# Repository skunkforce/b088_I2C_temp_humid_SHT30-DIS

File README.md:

# edgy_board number b088
This design is part of the [edgy board project](https://github.com/skunkforce/edgy_boards).

# getting started
This repository uses submodules. After cloning use the command 

```$ git submodule update --init --recursive```

to pull the submodules before opening the project with kicad. 

# Tests
Tests can be found in [TESTS.md](TESTS.md)

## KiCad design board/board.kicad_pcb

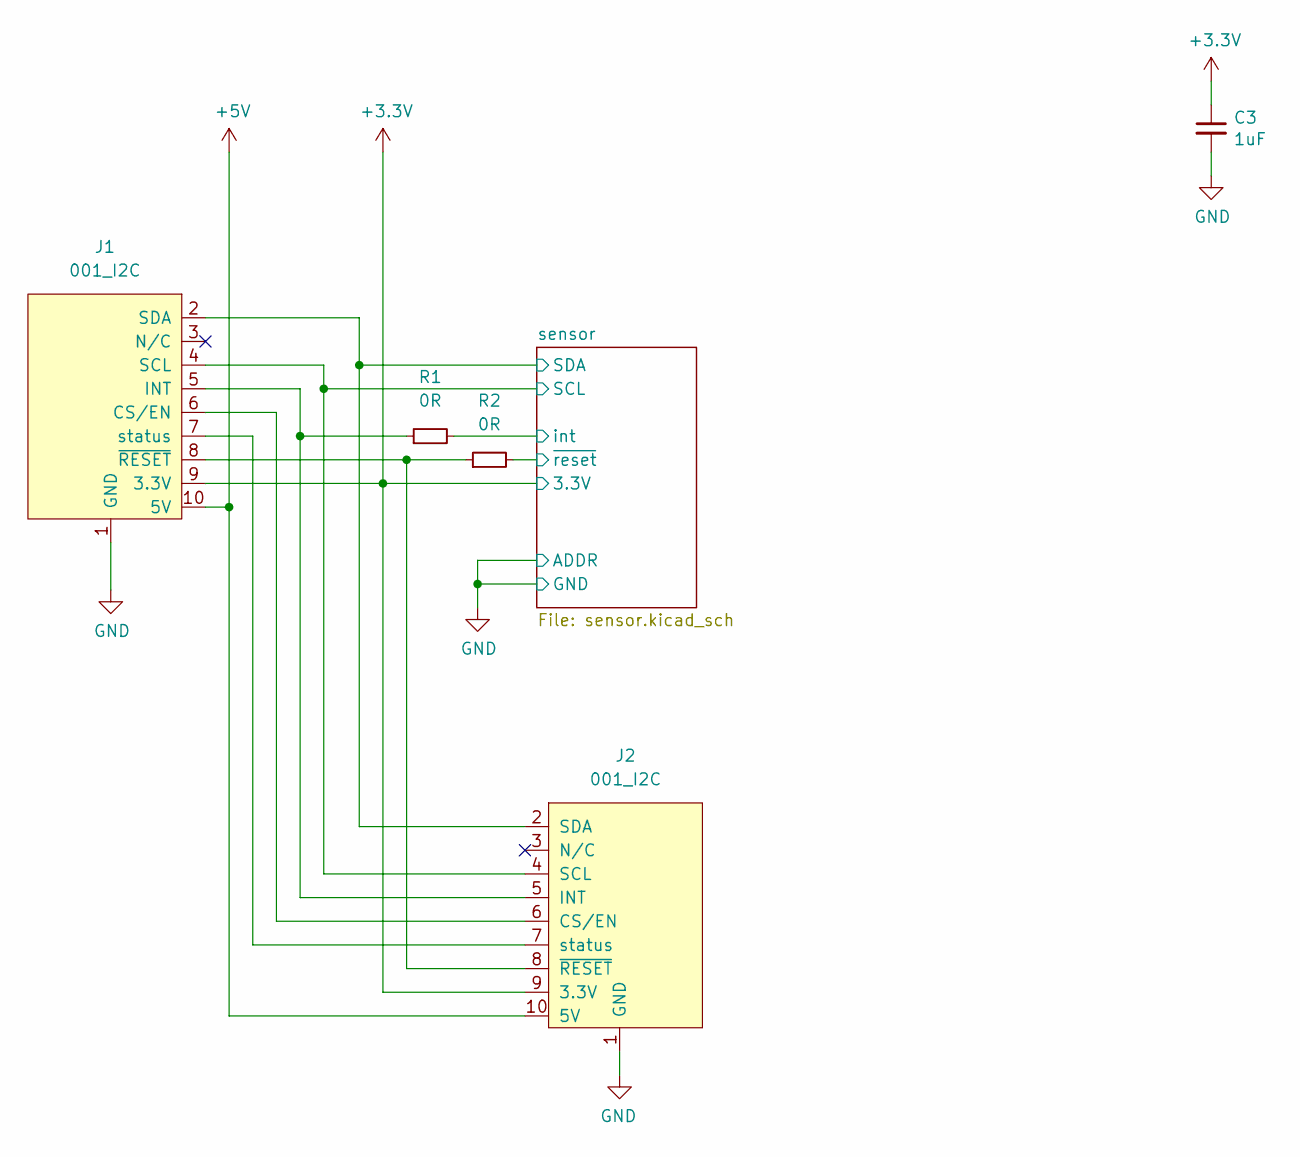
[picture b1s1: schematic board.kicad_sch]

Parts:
C3: 1uF; C_0603_1608Metric; Voltage 6.3V; lcsc C15849
J1: 001_I2C; on_edge_2x05_device
J2: 001_I2C; on_edge_2x05_host
R1, R2: 0R; R_0603_1608Metric; lcsc C21189

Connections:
+3.3V: C3.1, J1.9 (3.3V), J2.9 (3.3V); also elsewhere on the board
+5V: J1.10 (5V), J2.10 (5V)
/sensor/SCL: J1.4 (SCL), J2.4 (SCL); also elsewhere on the board
/sensor/SDA: J1.2 (SDA), J2.2 (SDA); also elsewhere on the board
/sensor/int: R1.2; also elsewhere on the board
/sensor/~reset: R2.2; also elsewhere on the board
GND: C3.2, J1.1 (GND), J2.1 (GND); also elsewhere on the board
unnamed: J1.6 (CS/EN), J2.6 (CS/EN)
unnamed: J1.5 (INT), J2.5 (INT), R1.1
unnamed: J1.7 (status), J2.7 (status)
unnamed: J1.8 (~RESET), J2.8 (~RESET), R2.1

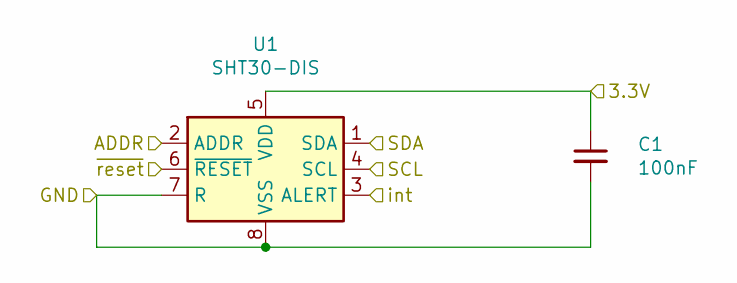
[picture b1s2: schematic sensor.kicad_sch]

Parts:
C1: 100nF; C_0603_1608Metric; lcsc C14663
U1: SHT30-DIS; Sensirion_DFN-8-1EP_2.5x2.5mm_P0.5mm_EP1.1x1.7mm; MPN SHT30-DIS-B10KS; Digi-Key_PN 1649-SHT30-DIS-B10KSCT-ND

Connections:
+3.3V: C1.1, U1.5 (VDD); also elsewhere on the board
/sensor/SCL: U1.4 (SCL); also elsewhere on the board
/sensor/SDA: U1.1 (SDA); also elsewhere on the board
/sensor/int: U1.3 (ALERT); also elsewhere on the board
/sensor/~reset: U1.6 (~RESET); also elsewhere on the board
GND: C1.2, U1.2 (ADDR), U1.7 (R), U1.8 (VSS), U1.9 (VSS); also elsewhere on the board

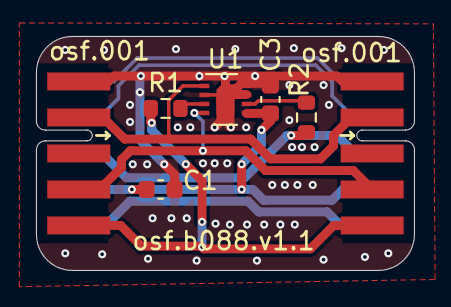
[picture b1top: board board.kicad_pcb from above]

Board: 2 copper layers, 21.0 x 13.0 mm, 7 parts (0 on the bottom side), 11 nets.

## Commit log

2023-04-16 initial
2023-04-16 used new normal rounded corners and added ground planes
2024-02-24 added LCSC part numbers
2024-07-07 updated I2C connector to current standard
